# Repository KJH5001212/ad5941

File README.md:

# AD5941 Potentiostat

nRF52832 + AD5941 3-electrode chronoamperometry potentiostat — firmware and Android control app.

Applies a fixed **+0.5 V** bias to the working electrode and measures **nA-level** current, streaming it over BLE to a phone app that drives run parameters and plots current vs time.

## `firmware/` — nRF52832 (Zephyr / NCS v3.4)

Drives the AD5941 analog front-end (potentiostat + LPTIA + ADC) over SPI.

- **Chronoamperometry** at fixed +0.5 V, **autorange** current (512 kΩ … 110 Ω, ~1 nA to µA).
- **Run modes**: continuous / timed (N s) / cycle (measure `on` s / rest `off` s, repeat).
- **BLE (Nordic UART Service)**: JSON commands (`start`/`stop`/`config`/`ack`/`status`); streams
  `{"d":[[seq,t_ms,current_nA,range],...]}`.
- **Lossless offline buffering**: samples are kept in a ring buffer with sequence numbers; the app
  ACKs received seq, and on reconnect the device re-transmits everything unacked — nothing is lost.
- **Power-aware BLE**: fast connection interval while measuring, slow (1.5 s) at rest (iOS-compatible,
  5 s supervision timeout).
- Vendored ADI AD5940 driver library under `src/ad5940lib/` (do not edit).

Build: NCS v3.4, `west build -b nrf52dk/nrf52832 firmware -d firmware/build`.
Flash (J-Link, low speed for signal integrity): `firmware/flash.jlink`.

## `android-app/` — Kotlin / Android

Scans and connects to the `ad5941` peripheral, sends run parameters, and visualizes results.

- Parameter form: potential (fixed 0.5 V), autorange, sample rate, run mode + cycle timing.
- Live **current-vs-time** graph, run/buffer/sync status, CSV recording + export to Downloads.
- Sends periodic `ack` so the device frees its lossless buffer; de-duplicates re-transmits by seq.

Build: Android Studio, or `cd android-app && ./gradlew :app:assembleDebug`.

## Status

Firmware and app build clean; AD5941 ADIID verified on hardware (0x4144). End-to-end BLE streaming
validation and dummy-cell current verification in progress.

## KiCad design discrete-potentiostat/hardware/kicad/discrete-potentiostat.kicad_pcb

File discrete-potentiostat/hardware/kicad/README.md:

# KiCad 회로도

`discrete-potentiostat.kicad_sch` — KiCad 7 포맷 (KiCad 7/8/9에서 열림), 심볼 전부 파일에 내장(라이브러리 설치 불필요).
`discrete-potentiostat.pdf` — 렌더링본.

## 검증 상태 (Rev A)

| 항목 | 상태 |
|---|---|
| 넷 연결 | ✅ **설계 넷리스트 38개 vs `kicad-cli` 추출 넷리스트 완전 일치** (`generator/check_nets.py`) |
| BQ51013BRHL 핀맵 | ✅ KiCad 공식 BQ51050BRHL 심볼(동일 계열 패키지) 기반 + 차이 핀(4 OUT, 10 EN1) 데이터시트 확인 |
| MCP73832 핀맵 | ✅ KiCad 공식 라이브러리 (1 STAT / 2 VSS / 3 VBAT / 4 VDD / 5 PROG) |
| MIC5205 핀맵 | ✅ KiCad 공식 라이브러리 (1 IN / 2 GND / 3 EN / 4 BYP / 5 OUT) |
| LPV802 DGK 핀맵 | ✅ 표준 듀얼 (1 OUTA / 2 −INA / 3 +INA / 4 V− / 5 +INB / 6 −INB / 7 OUTB / 8 V+) — VSSOP-8, OPA2391과 핀·풋프린트 호환 |
| REF35102 DBV 핀맵 | ✅ 데이터시트 확인 (1,2 GND / 3 EN / 4 VIN / 5 NR / 6 VREF) |
| nRF52832-QFAA 핀맵 (48+EP) | ✅ KiCad 공식 라이브러리 (MCU_Nordic:nRF52832-QFxx) |
| RF 프런트엔드 | ✅ Johanson 2450FM07A0029 = nRF52832 QFN 전용 매칭 LPF (벤더 확인) — 4핀 배치는 데이터시트 랜드패턴 따를 것 |
| DEC2/DEC3 미연결 | ✅ QFN48 레퍼런스 기준 (DEC2 확인됨) / ⚠️ DEC3는 최신 PS로 재확인 권장 |
| 충전전류 공식 | ✅ MCP73832: ICHG = 1000/RPROG = 20 mA · BQ51013B ILIM: RILIM = 250/IMAX |

**칩다운 전환(2026-07-10)**: MDBT42Q 모듈 → nRF52832-QFAA 베어칩. RF 체인은
ANT(30) → FL1(매칭 LPF) → R15(0R)/C34(DNP) 튜닝 슬롯 → 칩안테나. RF 레이아웃은 Nordic
QFN48 레퍼런스를 트레이스 형상까지 복사하고, 실보드에서 VNA로 안테나 튜닝할 것.

## 핀 할당 (nRF52832)

| 기능 | 핀 | QFN48 핀 번호 |
|---|---|---|
| SAADC 차동 N (VREF 1.024 V) | P0.02/AIN0 | 4 |
| SAADC 차동 P (TIA 출력) | P0.03/AIN1 | 5 |
| VBAT 모니터 | P0.04/AIN2 | 6 |
| AFE 전원 (high-drive) | P0.06 | 8 |
| 상태 LED | P0.07 | 9 |
| 충전 상태 (STAT, 100k 풀업) | P0.08 | 10 |
| RESET / SWD | P0.21(24) / SWDCLK(25) / SWDIO(26) | — |

## PCB (`discrete-potentiostat.kicad_pcb`) — RevC

**23.4×22 mm, 6층, 양면 실장** (2026-07-11 RevC — RevB 26×24 대비 면적 **-17.5%**).
크기 하한 근거: 폭 = 배터리 탭 패드(중심 ±9.8 + 패드 1.4 + 엣지 0.3 ≈ 23.0),
높이 = 셀 존 Ø21 + 여유. **이보다 더 줄이려면 배터리/탭 구조 자체를 바꿔야 함.**
IC 전부 윗면; 뒷면은 코너 포켓 4곳(R1·R2·TH1 좌상 / R3 우하 / R5·R6·C15 좌하)만 사용
— 뒷면 중앙 **Ø21 mm 원**(Cmts 표시)은 LIR2032 탭셀 전용. J2(SWD)·TP1-3은 앞면 우측 열로
이동(배터리와 충돌 방지 + 납땜 접근성), R4·R10/C21(DNP)은 앞면 여유 공간.
스택업: **L1 신호/RF · L2 GND · L3 배선 · L4 배선 · L5 GND · L6 신호+배터리 패드**.
설계규칙(보드에 저장): 트랙 최소 0.09 / 클리어런스 0.09 / 비아 0.4/0.2 — JLC 6층 표준 공정 내.

| 항목 | 상태 |
|---|---|
| 배치 | ✅ 겹침 0 · 보드이탈 0 · 배터리존 침범 0 (`check_pcb.py`) — J1/J2는 **Ø1.0 mm 원형 납땜 패드**(와이어 직납, 피치 1.8 mm) |
| GND | ✅ L2·L5 통짜 플레인 + F/B 포어 + 스티칭 비아, 고립 동박 0 |
| RF 급전 | ✅ ANT(U3.30)→FL1→pi 슬롯(C35/R15/C34)→칩안테나. **E1 은 데이터시트(36S0021A Rev4.1) 확정 4단자 랜드패턴** — 1·4 Feed(브리지 급전), 2·3 GND(좌측 포어로 0.3mm 스트립), 에지 수직 장착 |
| 신호 배선 | ✅ **전 넷 100% 배선 완료** (77넷, 미결선 0) — 자동배선 + 마지막 4링크(DCC/DEC1/ADC_P/CLAMP2)는 검증된 수동 경로(`close4.py`), 비아-인-패드 2곳(U3.47, C30) 포함 |
| DRC | ✅ `drc-report.txt`: **동박 위반 0** (미결선 0 · 클리어런스 0 · 홀 0 · 엣지 0 · 고립 0). 남은 항목은 실크 겹침/코트야드/서멀 릴리프 경고성 코스메틱 |

### 4층 축소 검토 결과 (2026-07-11)

**불가 판정.** 같은 배치(23.4×22 양면)에서 4층(배선층 3개: F/In2/B)으로 세 가지 전략
(프레시, 우선순위 선배선, AGGRO 립업)을 시도했으나 최소 12~22패드 미결선으로 수렴 실패.
U3 서쪽 핀 탈출과 U1 QFN 코너가 배선층 4개(6층)를 요구함. 4층을 원하면 보드를
~26×24 이상으로 키우고 단면 실장로 돌아가는 트레이드오프가 필요할 것으로 추정
(6층 유지 권장 — JLC 기준 6층 프로토 비용 차이는 수량 적을 때 크지 않음).

주의: 비아-인-패드 2곳(U3.47 DCC, C30.1 DEC1)과 U1.47 비아는 리플로우 시 솔더 위킹
가능성이 있음 — 프로토 수조립에서는 문제없고, 양산 시 via tenting/plugging 지정 권장.

### 남은 작업 (KiCad GUI에서 배선 불필요!)

1. 보드 열기 → `B`(존 채우기) → DRC 실행해 동박 위반 0 확인
2. 커스텀 풋프린트 랜드패턴 대조: **E1 완료**(36S0021A Rev4.1 반영) / FL1·코일 패드는 데이터시트 대조 남음
3. 실크 정리(선택) → File → Fabrication Outputs → Gerber 출력
4. 안테나는 실보드에서 VNA로 튜닝 (R15 0R ↔ C34/C35 DNP 슬롯)

## 재생성 방법

```bash
sudo apt install kicad kicad-symbols   # 공식 심볼 라이브러리 필요
cd generator
python3 extract_syms.py                # 시스템 라이브러리에서 베이스 심볼 추출
python3 gen_sch.py                     # ../discrete-potentiostat.kicad_sch 생성
kicad-cli sch export netlist --output out.net ../discrete-potentiostat.kicad_sch
python3 check_nets.py                  # 넷리스트 일치 확인 (RESULT: PASS 확인)
python3 gen_pcb.py                     # ../discrete-potentiostat.kicad_pcb 생성 (pcbnew API)
python3 check_pcb.py                   # 배치 겹침/보드이탈 검사 (flagged: 0 확인)
python3 route_pcb.py                   # 자동배선 (GND 스티칭 + A* 립업 라우터, 6층)
RESUME=1 python3 route_pcb.py          # 기존 배선 보존, 미결선만 이어서 배선
./route_loop.sh                        # DRC→미결선 목록→RESUME 수렴 루프 (×4)
# todo_override.json(DRC 미결선 목록)을 두면 RESUME이 그 목록만 공략
# PRIORITY=NET1,NET2 환경변수로 특정 넷을 최우선 배선 (막힌 코너 공략용)
```

배선이 특정 코너에서 계속 실패하면: 그 통로를 점거한 넷들의 트랙을 지우고
todo_override.json에 [실패넷들 우선, 걷어낸 넷들 나중] 순서로 넣은 뒤
`PRIORITY=... RESUME=1`로 재실행 (U1 QFN 코너가 이 방법으로 뚫렸음).
`gnd_fix.py`(GND 고아 패드/고립 섬 스티칭)와 `copper_fix.py`(RF 경로 검증 재배선,
좌표 하드코딩된 1회성 스크립트)는 기록용으로 남겨둠.

배치를 바꾸려면 `gen_pcb.py`의 `PLACE` 좌표를 수정하거나, KiCad GUI에서 직접 옮기면 된다
(회로 연결은 라벨 기반이라 심볼을 옮겨도 넷은 유지됨).

## 회로도에 박혀 있는 주의사항 (DESIGN NOTES 텍스트 블록)

1. 충전은 2단: BQ51013B(Qi→5V, ILIM 100 mA) + MCP73832(20 mA/4.2 V, 종지 1.5 mA) — BQ51050B 직접충전(TI <200 mA 비권장) 대체
2. 공진탱크는 L=47 µH 기준 — 코일 변경 시 C1/C2 재계산
3. 칩다운 RF: Nordic QFN48 레퍼런스 레이아웃 복사 + 실보드 안테나 튜닝(R15/C34 슬롯), DEC3 최신 PS 확인
4. WE 노드 가드링(VREF 구동), 플럭스 세정
5. R10/C21(보상망)은 DNP — CE-RE 루프 발진 시만 실장
6. LIR2032 무보호 — 3.0 V 미만 System OFF 펌웨어 필수

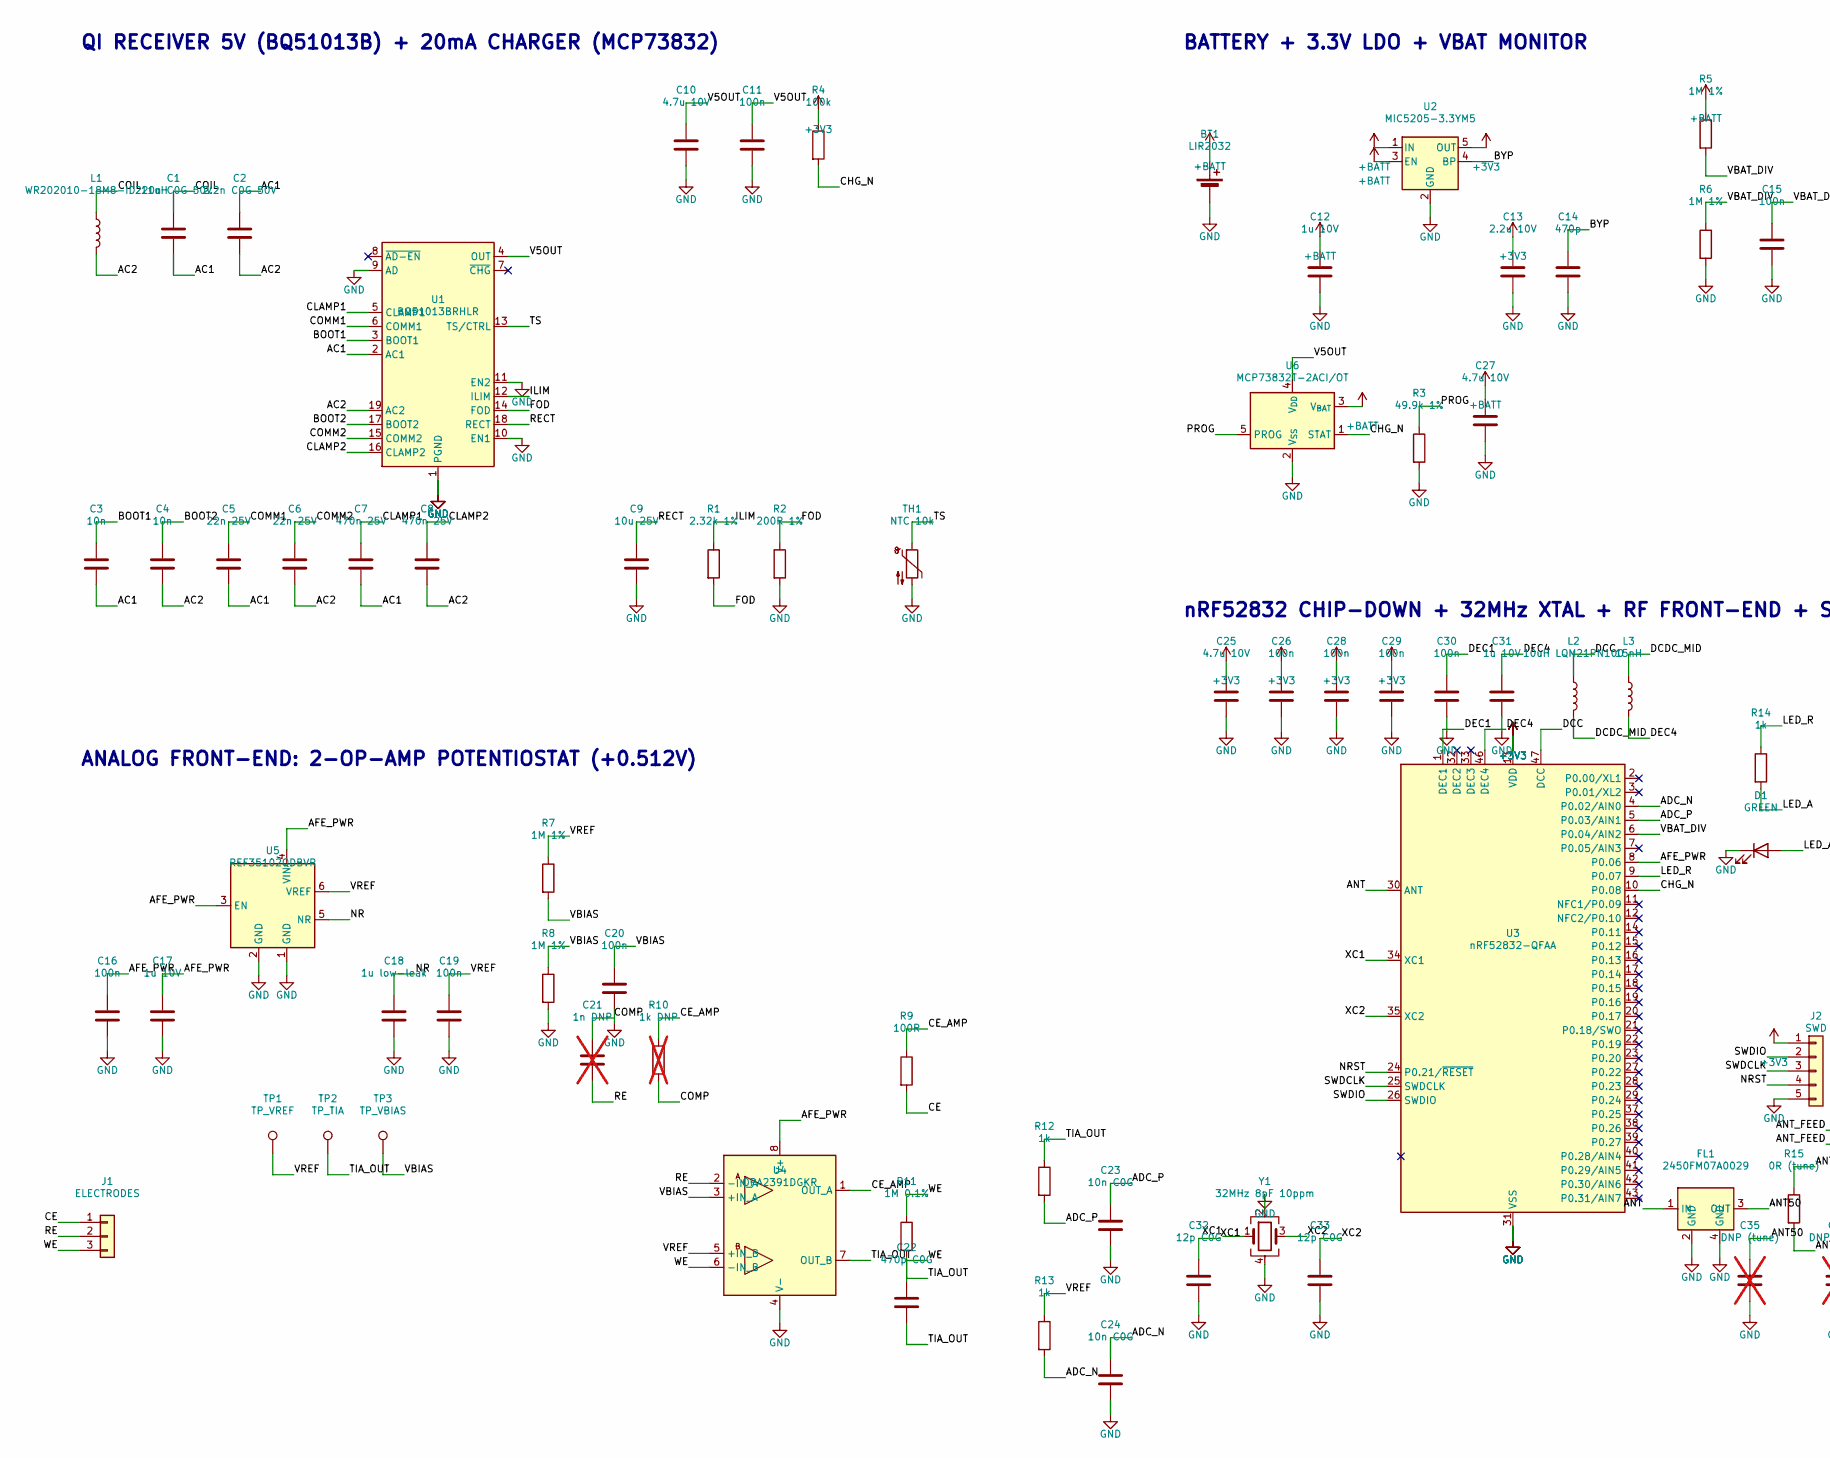
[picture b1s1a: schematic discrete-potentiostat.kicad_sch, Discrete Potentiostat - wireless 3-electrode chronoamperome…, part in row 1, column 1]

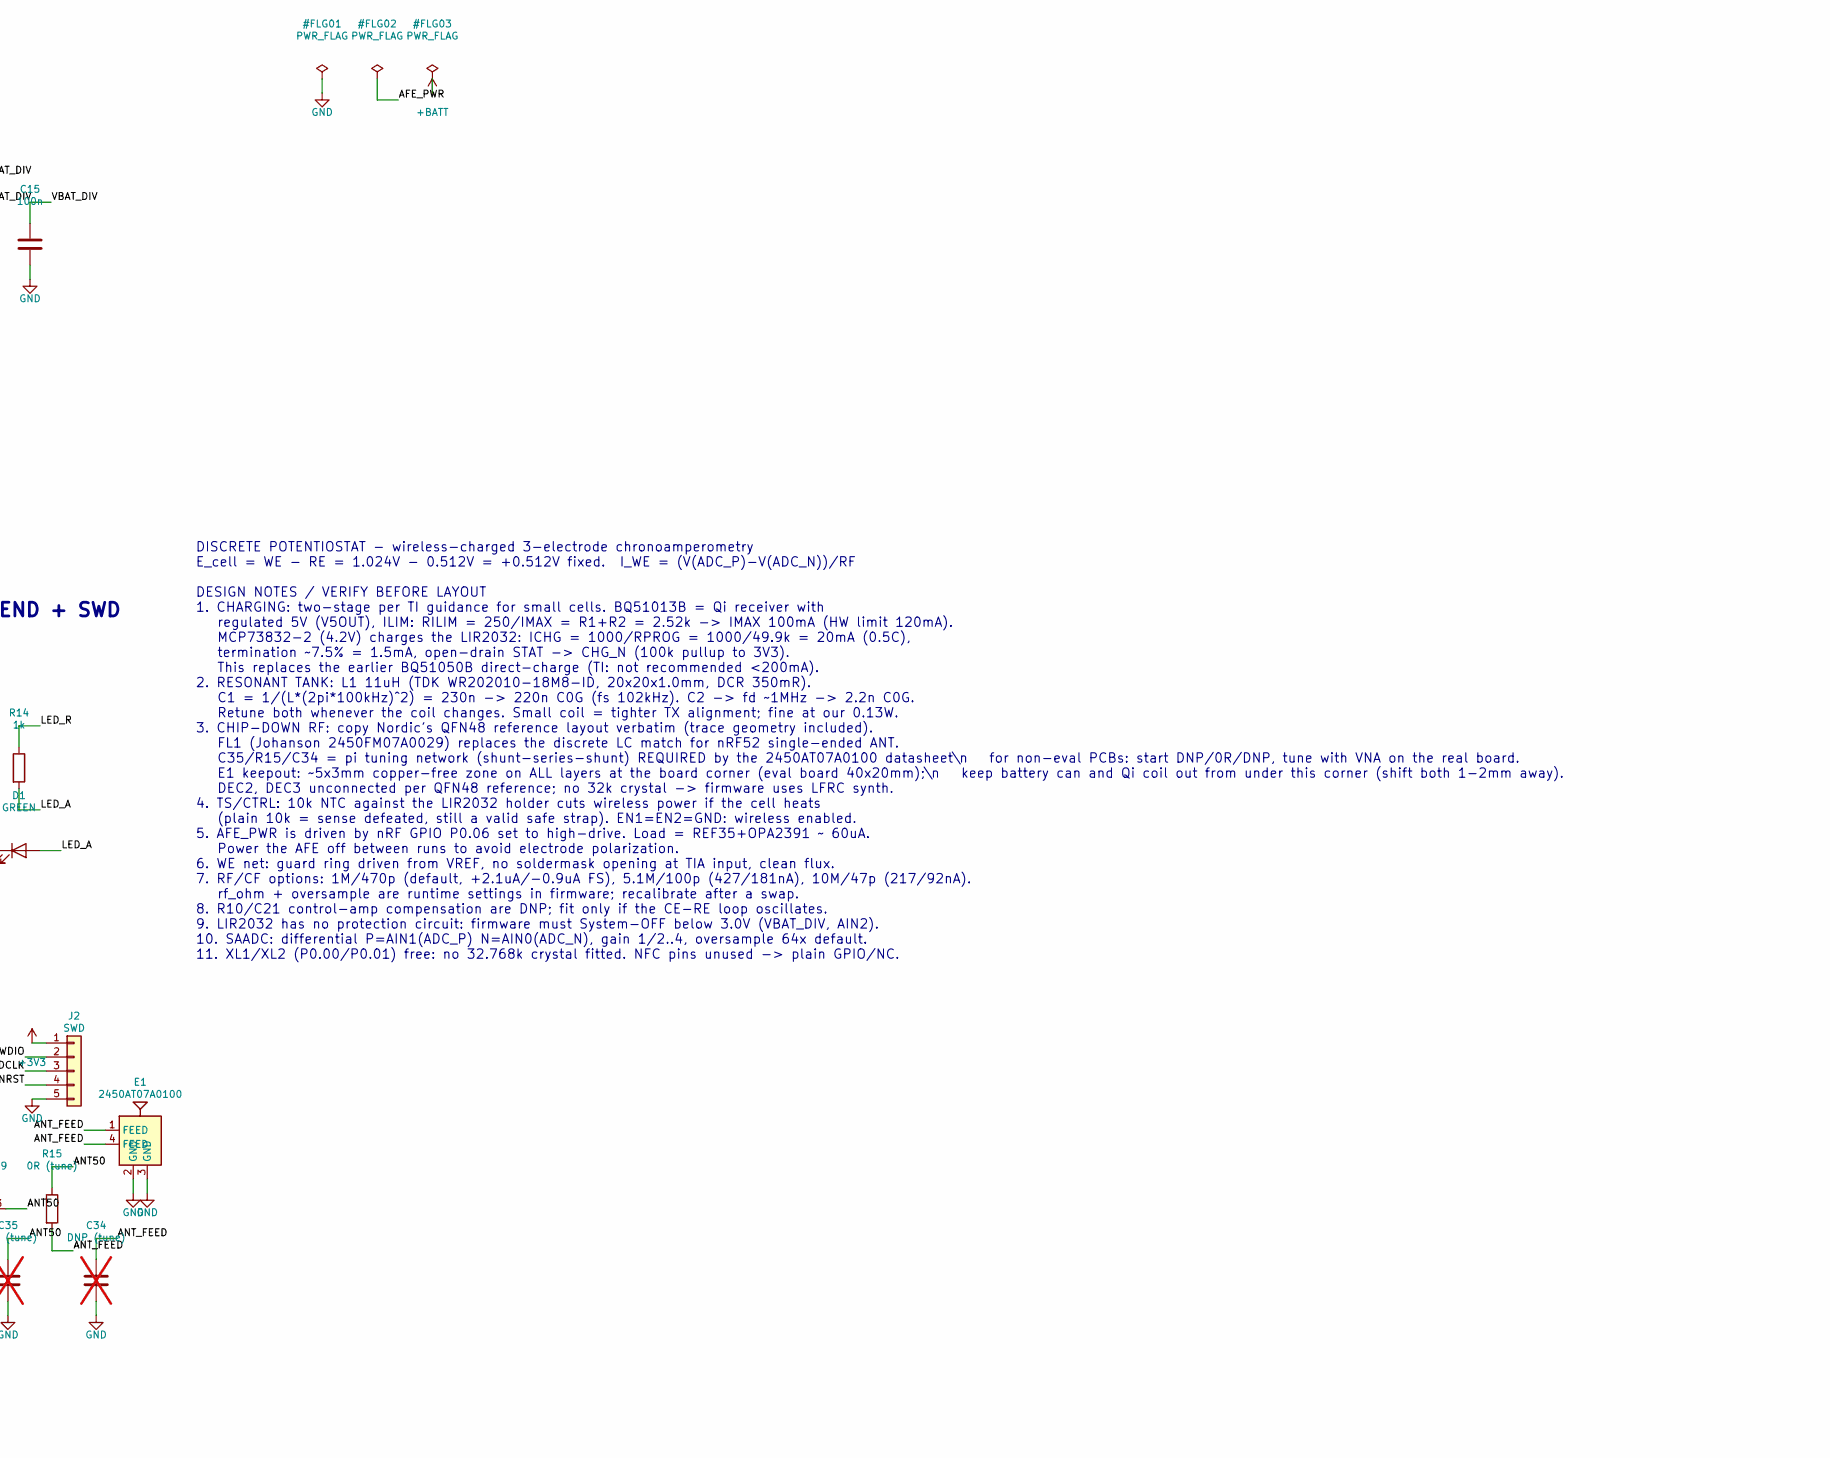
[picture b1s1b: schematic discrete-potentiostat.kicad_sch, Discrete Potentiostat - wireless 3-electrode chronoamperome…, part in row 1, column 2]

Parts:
BT1: LIR2032; BatteryHolder_Keystone_3034_1x20mm
C1: 220n C0G 50V; C_1210_3225Metric
C2: 2.2n C0G 50V; C_0603_1608Metric
C3, C4: 10n; C_0402_1005Metric
C5, C6: 22n 25V; C_0402_1005Metric
C7, C8: 470n 25V; C_0603_1608Metric
C9: 10u 25V; C_0805_2012Metric
C10, C25, C27: 4.7u 10V; C_0603_1608Metric
C11, C15, C16, C19, C20, C26, C28, C29, C30: 100n; C_0402_1005Metric
C12, C17, C31: 1u 10V; C_0402_1005Metric
C13: 2.2u 10V; C_0603_1608Metric
C14: 470p; C_0402_1005Metric
C18: 1u low-leak; C_0603_1608Metric
C21: 1n DNP; C_0402_1005Metric; not fitted
C22: 470p C0G; C_0603_1608Metric
C23, C24: 10n C0G; C_0402_1005Metric
C32, C33: 12p C0G; C_0402_1005Metric
C34, C35: DNP (tune); C_0402_1005Metric; not fitted
D1: GREEN; LED_0603_1608Metric
E1: 2450AT07A0100; Johanson_2450AT07A0100
FL1: 2450FM07A0029; Johanson_0402_4pin
J1: ELECTRODES; SolderPads_1x03_D1.0mm
J2: SWD; SolderPads_1x05_D1.0mm
L1: WR202010-18M8-ID 11uH; TDK_WR202010
L2: 10uH LQM21PN100; L_0805_2012Metric
L3: 15nH; L_0402_1005Metric
R1: 2.32k 1%; R_0402_1005Metric
R2: 200R 1%; R_0402_1005Metric
R3: 49.9k 1%; R_0402_1005Metric
R4: 100k; R_0402_1005Metric
R5, R6, R7, R8: 1M 1%; R_0402_1005Metric
R9: 100R; R_0402_1005Metric
R10: 1k DNP; R_0402_1005Metric; not fitted
R11: 1M 0.1%; R_0603_1608Metric
R12, R13, R14: 1k; R_0402_1005Metric
R15: 0R (tune); R_0402_1005Metric
TH1: NTC 10k; R_0402_1005Metric
TP1: TP_VREF; TestPoint_Pad_D1.5mm
TP2: TP_TIA; TestPoint_Pad_D1.5mm
TP3: TP_VBIAS; TestPoint_Pad_D1.5mm
U1: BQ51013BRHLR; Texas_VQFN-RHL-20
U2: MIC5205-3.3YM5; SOT-23-5
U3: nRF52832-QFAA; QFN-48-1EP_6x6mm_P0.4mm_EP4.6x4.6mm
U4: OPA2391DGKR; VSSOP-8_3.0x3.0mm_P0.65mm
U5: REF35102QDBVR; SOT-23-6
U6: MCP73832T-2ACI/OT; SOT-23-5
Y1: 32MHz 8pF 10ppm; Crystal_SMD_3225-4Pin_3.2x2.5mm

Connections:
+3V3: C13.1, C25.1, C26.1, C28.1, C29.1, J2.1, R4.1, U2.5 (OUT), U3.13 (VDD), U3.36 (VDD), U3.48 (VDD)
+BATT: BT1.1 (+), C12.1, C27.1, R5.1, U2.1 (IN), U2.3 (EN), U6.3 (V_{BAT})
AC1: C1.2, C2.1, C3.2, C5.2, C7.2, U1.2 (AC1)
AC2: C2.2, C4.2, C6.2, C8.2, L1.2, U1.19 (AC2)
ADC_N: C24.1, R13.2, U3.4 (P0.02/AIN0)
ADC_P: C23.1, R12.2, U3.5 (P0.03/AIN1)
AFE_PWR: C16.1, C17.1, U3.8 (P0.06), U4.8 (V+), U5.3 (EN), U5.4 (VIN)
ANT: FL1.1 (IN), U3.30 (ANT)
ANT50: C35.1, FL1.3 (OUT), R15.1
ANT_FEED: C34.1, E1.1 (FEED), E1.4 (FEED), R15.2
BOOT1: C3.1, U1.3 (BOOT1)
BOOT2: C4.1, U1.17 (BOOT2)
BYP: C14.1, U2.4 (BP)
CE: J1.1, R9.2
CE_AMP: R9.1, R10.1, U4.1 (OUT_A)
CHG_N: R4.2, U3.10 (P0.08), U6.1 (STAT)
CLAMP1: C7.1, U1.5 (CLAMP1)
CLAMP2: C8.1, U1.16 (CLAMP2)
COIL: C1.1, L1.1
COMM1: C5.1, U1.6 (COMM1)
COMM2: C6.1, U1.15 (COMM2)
COMP: C21.1, R10.2
DCC: L2.1, U3.47 (DCC)
DCDC_MID: L2.2, L3.1
DEC1: C30.1, U3.1 (DEC1)
DEC4: C31.1, L3.2, U3.46 (DEC4)
FOD: R1.2, R2.1, U1.14 (FOD)
GND: BT1.2 (-), C9.2, C10.2, C11.2, C12.2, C13.2, C14.2, C15.2, C16.2, C17.2, C18.2, C19.2, C20.2, C23.2, C24.2, C25.2, C26.2, C27.2, C28.2, C29.2, C30.2, C31.2, C32.2, C33.2, C34.2, C35.2, D1.1 (K), E1.2 (GND), E1.3 (GND), FL1.2 (GND), FL1.4 (GND), J2.5, R2.2, R3.2, R6.2, R8.2, TH1.2, U1.1 (PGND), U1.9 (AD), U1.10 (EN1), U1.11 (EN2), U1.20 (PGND), U1.21 (PGND), U2.2 (GND), U3.31 (VSS), U3.45 (VSS), U3.49 (VSS), U4.4 (V-), U5.1 (GND), U5.2 (GND), U6.2 (V_{SS}), Y1.2, Y1.4
ILIM: R1.1, U1.12 (ILIM)
LED_A: D1.2 (A), R14.2
LED_R: R14.1, U3.9 (P0.07)
NR: C18.1, U5.5 (NR)
NRST: J2.4, U3.24 (P0.21/~RESET)
PROG: R3.1, U6.5 (PROG)
RE: C21.2, J1.2, U4.2 (-IN_A)
RECT: C9.1, U1.18 (RECT)
SWDCLK: J2.3, U3.25 (SWDCLK)
SWDIO: J2.2, U3.26 (SWDIO)
TIA_OUT: C22.2, R11.2, R12.1, TP2.1, U4.7 (OUT_B)
TS: TH1.1, U1.13 (TS/CTRL)
V5OUT: C10.1, C11.1, U1.4 (OUT), U6.4 (V_{DD})
VBAT_DIV: C15.1, R5.2, R6.1, U3.6 (P0.04/AIN2)
VBIAS: C20.1, R7.2, R8.1, TP3.1, U4.3 (+IN_A)
VREF: C19.1, R7.1, R13.1, TP1.1, U4.5 (+IN_B), U5.6 (VREF)
WE: C22.1, J1.3, R11.1, U4.6 (-IN_B)
XC1: C32.1, U3.34 (XC1), Y1.1
XC2: C33.1, U3.35 (XC2), Y1.3

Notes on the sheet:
DISCRETE POTENTIOSTAT - wireless-charged 3-electrode chronoamperometry E_cell = WE - RE = 1.024V - 0.512V = +0.512V fixed. I_WE = (V(ADC_P)-V(ADC_N))/RF DESIGN NOTES / VERIFY BEFORE LAYOUT 1. CHARGING: two-stage per TI guidance for small cells. BQ51013B = Qi receiver with regulated 5V (V5OUT), ILIM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
QI RECEIVER 5V (BQ51013B) + 20mA CHARGER (MCP73832)
BATTERY + 3.3V LDO + VBAT MONITOR
ANALOG FRONT-END: 2-OP-AMP POTENTIOSTAT (+0.512V)
nRF52832 CHIP-DOWN + 32MHz XTAL + RF FRONT-END + SWD

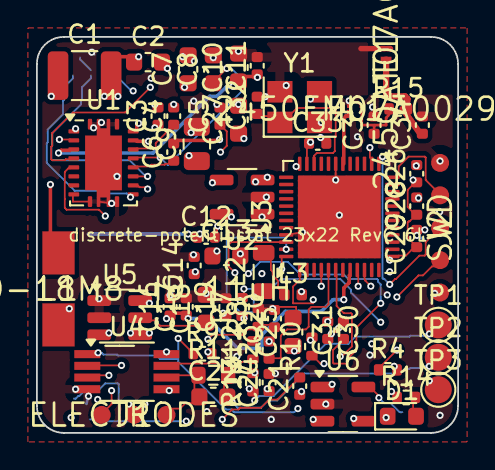
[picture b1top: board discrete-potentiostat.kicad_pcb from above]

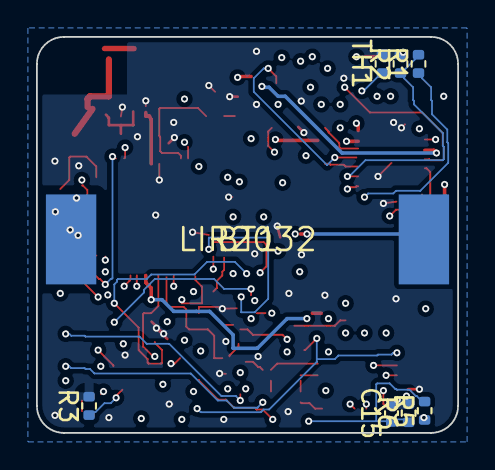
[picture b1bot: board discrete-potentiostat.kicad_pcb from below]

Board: 6 copper layers, 23.4 x 22.0 mm, 70 parts (8 on the bottom side), 47 nets.

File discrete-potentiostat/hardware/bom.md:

# BOM

레퍼런스는 `hardware/kicad/discrete-potentiostat.kicad_sch`와 1:1 일치.

## IC / 모듈 / 배터리 / 기구

| Ref | 부품 | 패키지 | 역할 |
|---|---|---|---|
| U1 | BQ51013BRHLR | VQFN-20 (RHL) | Qi 수신, 레귤레이티드 5 V 출력 |
| U6 | MCP73832T-2ACI/OT | SOT-23-5 | 리튬 충전기 4.2 V / 20 mA, 종지 ~1.5 mA |
| U2 | MIC5205-3.3YM5 | SOT-23-5 | 3.3 V LDO |
| U3 | nRF52832-QFAA | QFN48 6×6 (칩다운) | MCU + BLE + SAADC |
| Y1 | 수정 32 MHz, CL 8 pF, ±10 ppm | 3225 | HFXO (BLE 필수) |
| FL1 | Johanson 2450FM07A0029 | 0402 4-pin | nRF52 전용 임피던스 매칭 LPF (디스크리트 매칭 대체) |
| E1 | Johanson 2450AT07A0100 | **1.0×0.5×0.37 mm (0402), 4단자** | 2.4 GHz 칩안테나 — 단자 1·4=Feed, **2·3=GND**(데이터시트 36S0021A Rev4.1 확정, 좌측 GND 포어에 스트립 연결). 전층 구리금지 ~5×3 mm 킵아웃 + pi 슬롯(C35/R15/C34) 실보드 튜닝 필수 |
| U4 | LPV802DGKR | VSSOP-8 | A: 컨트롤 앰프 / B: TIA — 나노파워 0.32 µA/ch, Ib 0.1 pA |
| U5 | REF35102QDBVR | SOT-23-6 | 1.024 V 레퍼런스 |
| BT1 | LIR2032 **탭 용접형(솔더탭)** | 뒷면 패드 2개 | 3.7 V / ~40 mAh — Keystone 3034 홀더는 폭 27 mm로 23.4×22 mm 보드에 안 들어가 탭셀 채택 (뒷면 중앙 Ø21 배치구역 확보). 보호회로 없음 — 펌웨어 컷오프 필수 |
| L1 | TDK WR202010-18M8-ID | **20×20×1.0 mm** | Qi RX 코일, **11 µH ±5%**, DCR 350 mΩ, ~$3.6 |
| D1 | LED GREEN 0603 | — | 상태 표시 (P0.07) |
| J1 | 납땜 패드 Ø1.0 mm ×3 | 피치 1.8 mm | 전극 CE/RE/WE 와이어 직납 |
| J2 | 납땜 패드 Ø1.0 mm ×5 | 피치 1.8 mm | SWD 와이어 직납 (3V3/SWDIO/SWDCLK/RESET/GND) |
| TP1–TP3 | 테스트포인트 | Ø1.5 mm | VREF / TIA_OUT / VBIAS |

## 수동소자 (회로도 Ref 순)

| Ref | 값 | 사양 | 역할 |
|---|---|---|---|
| C1 | 220 nF | C0G 50 V, 1210 | 직렬 공진 (fs≈102 kHz, L=11 µH 기준) |
| C2 | 2.2 nF | C0G 50 V | 병렬 공진 (fd≈1 MHz) |
| C3, C4 | 10 nF | 25 V | BOOT1/BOOT2 → AC1/AC2 |
| C5, C6 | 22 nF | 25 V | COMM1/COMM2 → AC1/AC2 |
| C7, C8 | 470 nF | 25 V | CLAMP1/CLAMP2 → AC1/AC2 |
| C9 | 10 µF | 25 V, 0805 | RECT |
| C10, C11 | 4.7 µF + 100 nF | 10 V | V5OUT (BQ51013B OUT = MCP73832 입력) |
| C12 | 1 µF | 10 V | LDO 입력 |
| C13 | 2.2 µF | 10 V | LDO 출력 (세라믹, ≥1 µF) |
| C14 | 470 pF | — | MIC5205 BYP (노이즈 저감) |
| C15 | 100 nF | — | VBAT_DIV 필터 |
| C16, C17 | 100 nF + 1 µF | — | AFE_PWR 디커플링 |
| C18 | 1 µF | 저누설 | REF35 NR (2.7 Hz LPF) |
| C19 | 100 nF | — | VREF 출력 (REF35 최소 0.1 µF) |
| C20 | 100 nF | — | VBIAS(0.512 V) 필터 |
| C21 | 1 nF | **DNP** | 컨트롤 앰프 보상 (발진 시만 실장) |
| C22 | 470 pF | C0G | CF — TIA 대역제한 (RF 교체 시 짝 교체) |
| C23, C24 | 10 nF | C0G | SAADC 입력 RC |
| C25 | 4.7 µF | 10 V | VDD 벌크 |
| C26, C28, C29 | 100 nF ×3 | — | VDD 핀 13/36/48 디커플링 |
| C30 | 100 nF | — | DEC1 |
| C31 | 1 µF | — | DEC4 (DC/DC 출력) |
| C32, C33 | 12 pF ×2 | C0G | 32 MHz 로드캡 (CL 8 pF 기준) |
| C34, C35 | (DNP) ×2 | C0G | 안테나 pi 튜닝 션트 슬롯 |
| C27 | 4.7 µF | 10 V | 배터리(+BATT) 측 |
| R1 | 2.32 kΩ | 1% | ILIM 상단 — IMAX = 250/(R1+R2) ≈ 100 mA (5V 출력 전류 한도) |
| R2 | 200 Ω | 1% | RFOD (FOD 탭, 캘리브레이션 시작값) |
| R3 | 49.9 kΩ | 1% | MCP73832 PROG — ICHG = 1000/RPROG = 20 mA |
| R4 | 100 kΩ | — | /CHG 풀업 → 3V3 |
| R5, R6 | 1 MΩ ×2 | 1% | VBAT 모니터 분압 → AIN2 |
| R7, R8 | 1 MΩ ×2 | 1% 페어 | 1:1 바이어스 분압 → VBIAS 0.512 V |
| R9 | 100 Ω | — | CE 직렬 (안정성) |
| R10 | 1 kΩ | **DNP** | 컨트롤 앰프 보상 (C21과 직렬) |
| R11 | 1 MΩ | 0.1% thin-film, ≤50 ppm/°C | **RF** (5.1 M/10 M 교체 풋프린트) |
| R12, R13 | 1 kΩ ×2 | — | SAADC 입력 RC |
| R14 | 1 kΩ | — | LED 직렬 |
| R15 | 0 Ω | 0402 | 안테나 pi 튜닝 직렬 슬롯 (C35·C34 션트와 함께 션트-직렬-션트 — 2450AT07A0100 데이터시트 요구) |
| L2, L3 | 10 µH (LQM21PN100) + 15 nH | 0805/0402 | DCC→DEC4 DC/DC 인덕터 (미사용 시 LDO 모드로 무해) |
| TH1 | NTC 10 kΩ | B≈3380 | BQ51013B TS/CTRL — LIR2032 홀더 밀착 배치 |

## 참고

- RF/CF 교체 옵션: 1 M/470 p(기본) · 5.1 M/100 p · 10 M/47 p — 펌웨어 `rf_ohm`/`oversample`은 런타임 설정.
- U4 업그레이드 옵션(핀호환): LPV812(오프셋 ±0.3 mV 정밀형) · OPA2391(fA급 Ib, 22 µA/ch — 이전 채택품).
- 충전 체인은 2단(Qi 5 V → 저전류 충전기): BQ51050B 직접충전이 TI 공식으로 <200 mA 비권장이라 교체됨 (`design.md` §5).
- 초소형화 시 동일 토폴로지로 BQ51003(DSBGA-28) + BQ25100(DSBGA-6) 교체 가능.
- MCU는 칩다운(모듈 미사용) — 의도적 방사체 무선 인증(KC/FCC/CE RED) + 안테나 튜닝 필요. 결정 근거는 `module-vs-chipdown.md`.

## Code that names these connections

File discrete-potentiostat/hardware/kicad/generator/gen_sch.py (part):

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    add('TP2','Connector:TestPoint', 70, 235, 'TP_TIA','TestPoint:TestPoint_Pad_D1.5mm', {'1':'TIA_OUT'})
    add('TP3','Connector:TestPoint', 80, 235, 'TP_VBIAS','TestPoint:TestPoint_Pad_D1.5mm', {'1':'VBIAS'})
    # ---------------- nRF module ----------------
    nrf_pins = {'1':'DEC1', '4':'ADC_N', '5':'ADC_P', '6':'VBAT_DIV',
                '8':'AFE_PWR', '9':'LED_R', '10':'CHG_N',
                '13':V3, '24':'NRST', '25':'SWDCLK', '26':'SWDIO',
                '30':'ANT', '31':GND, '34':'XC1', '35':'XC2',
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   DEC2, DEC3 unconnected per QFN48 reference; no 32k crystal -> firmware uses LFRC synth.
4. TS/CTRL: 10k NTC against the LIR2032 holder cuts wireless power if the cell heats
   (plain 10k = sense defeated, still a valid safe strap). EN1=EN2=GND: wireless enabled.
5. AFE_PWR is driven by nRF GPIO P0.06 set to high-drive. Load = REF35+OPA2391 ~ 60uA.
   Power the AFE off between runs to avoid electrode polarization.
6. WE net: guard ring driven from VREF, no soldermask opening at TIA input, clean flux.
7. RF/CF options: 1M/470p (default, +2.1uA/-0.9uA FS), 5.1M/100p (427/181nA), 10M/47p (217/92nA).
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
